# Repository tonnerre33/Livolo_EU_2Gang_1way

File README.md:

# Linovo_EU_2Gang_1way

## THIS NODE IS CURRENTLY IN DEVELOP
## YOU CAN SEE AND TEST THE DEV BRANCH AT YOUR OWN RISKS

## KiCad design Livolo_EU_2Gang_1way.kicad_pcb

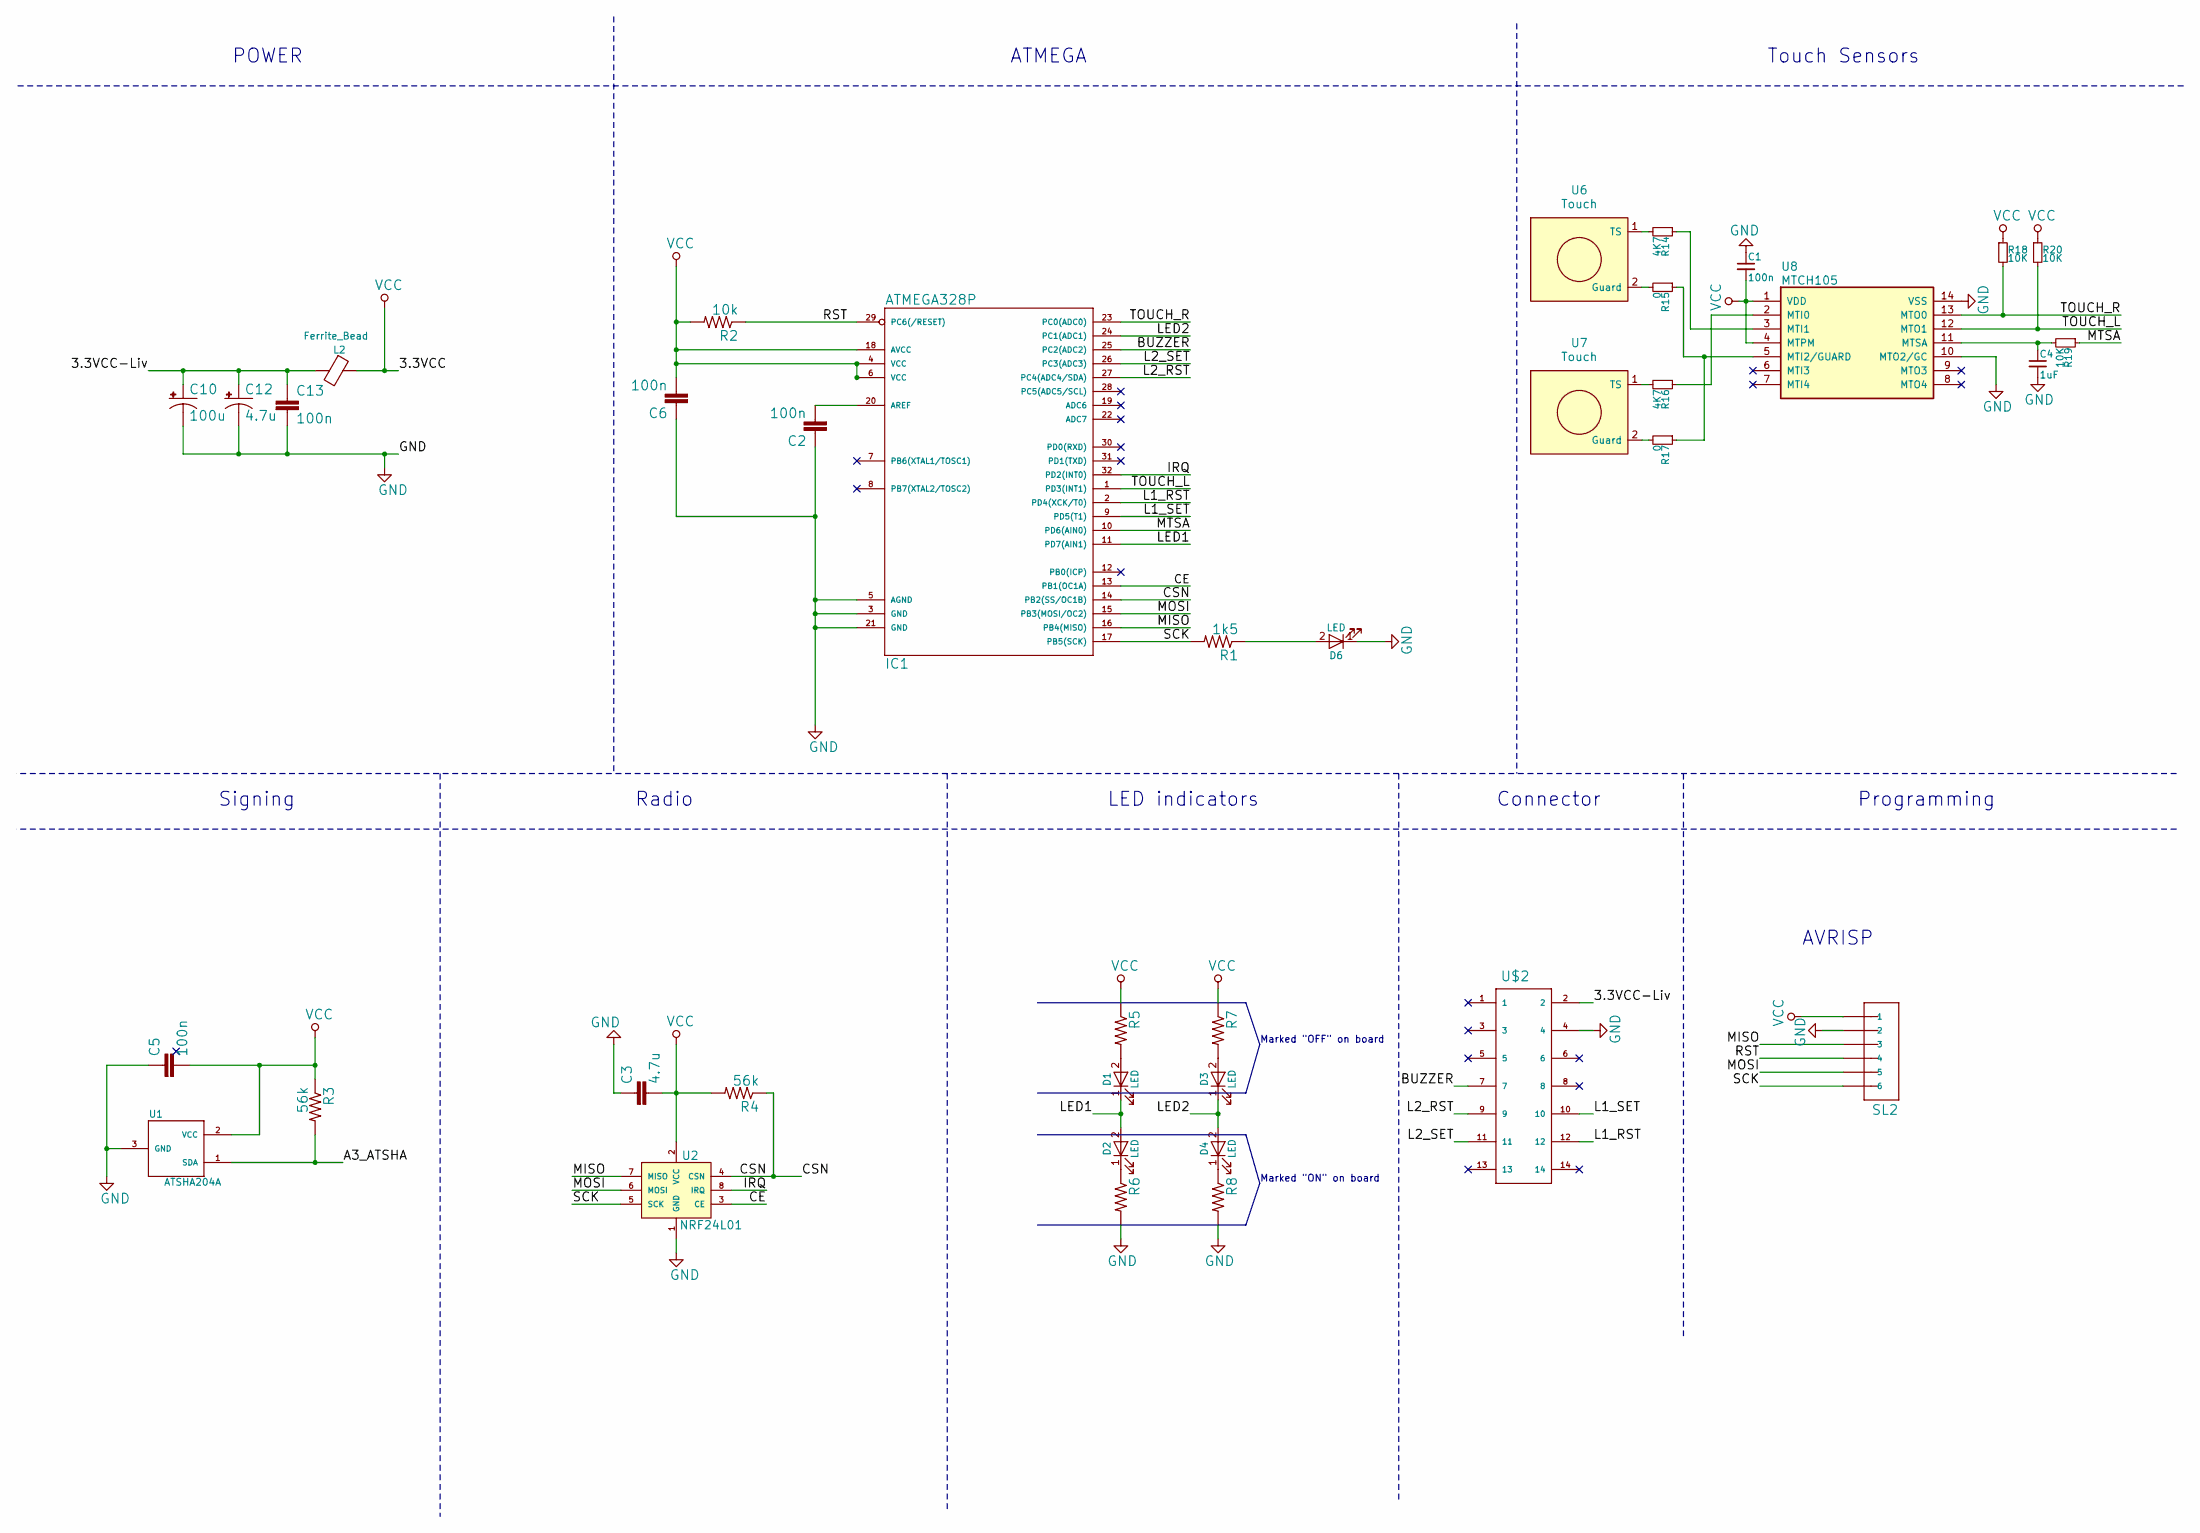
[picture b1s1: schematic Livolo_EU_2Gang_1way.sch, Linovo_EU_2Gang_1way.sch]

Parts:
C1, C5: 100n; C_0603_HandSoldering
C2, C6: 100n; C_0402
C3: 4.7u; C_0603_HandSoldering
C4: 1uF; C_0603_HandSoldering
C10: 100u; EIA3216; Rating X5R/10V
C12: 4.7u; EIA3216; Rating X5R/10V
C13: 100n; C_0603_HandSoldering; Rating X5R/10V
D1, D2, D3, D4, D6: LED; LED_0603
IC1: ATMEGA328P; TQFP32-08
L2: Ferrite_Bead; R_0603_HandSoldering
R1: 1k5; R_0603_HandSoldering
R2: 10k; R_0603_HandSoldering
R3, R4: 56k; R_0603_HandSoldering
R5, R6, R7, R8: R_0603_HandSoldering
R14, R16: 4K7; R_0603
R15, R17: 0; R_0603
R18, R19, R20: 10K; R_0603
SL2: 1X06-1MM
U1: ATSHA204A; SOT23-3
U2: NRF24L01; NRF24L01-SMD
U6, U7: Touch; livolo_ts_guard
U8: MTCH105; SSOP-14_5.3x6.2mm_Pitch0.65mm
U$2: CONNECTOR_02_X_072MM_SPACING; CONNECTOR_02_X_07_2MM

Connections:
/3.3VCC-Liv: C10.+, C12.+, C13.1, L2.2, U$2.2
/A3_ATSHA: R3.2, U1.1 (SDA)
/BUZZER: IC1.25 (PC2(ADC2)), U$2.7
/CE: IC1.13 (PB1(OC1A)), U2.3 (CE)
/CSN: IC1.14 (PB2(SS/OC1B)), R4.1, U2.4 (CSN)
/IRQ: IC1.32 (PD2(INT0)), U2.8 (IRQ)
/L1_RST: IC1.2 (PD4(XCK/T0)), U$2.12
/L1_SET: IC1.9 (PD5(T1)), U$2.10
/L2_RST: IC1.27 (PC4(ADC4/SDA)), U$2.9
/L2_SET: IC1.26 (PC3(ADC3)), U$2.11
/LED1: D1.1 (K), D2.2 (A), IC1.11 (PD7(AIN1))
/LED2: D3.1 (K), D4.2 (A), IC1.24 (PC1(ADC1))
/MISO: IC1.16 (PB4(MISO)), SL2.3, U2.7 (MISO)
/MOSI: IC1.15 (PB3(MOSI/OC2)), SL2.5, U2.6 (MOSI)
/MTSA: IC1.10 (PD6(AIN0)), R19.1
/RST: IC1.29 (PC6(/RESET)), R2.1, SL2.4
/SCK: IC1.17 (PB5(SCK)), R1.2, SL2.6, U2.5 (SCK)
/TOUCH_L: IC1.1 (PD3(INT1)), R20.2, U8.12 (MTO1)
/TOUCH_R: IC1.23 (PC0(ADC0)), R18.2, U8.13 (MTO0)
GND: C1.1, C2.1, C3.1, C4.2, C5.1, C6.1, C10.-, C12.-, C13.2, D6.1 (K), IC1.3 (GND), IC1.5 (AGND), IC1.21 (GND), R6.2, R8.2, SL2.2, U1.3 (GND), U2.1 (GND), U8.10 (MTO2/GC), U8.14 (VSS), U$2.4
unnamed: C2.2, IC1.20 (AREF)
unnamed: C4.1, R19.2, U8.11 (MTSA)
unnamed: D1.2 (A), R5.2
unnamed: D2.1 (K), R6.1
unnamed: D3.2 (A), R7.2
unnamed: D4.1 (K), R8.1
unnamed: D6.2 (A), R1.1
unnamed: R14.1, U8.3 (MTI1)
unnamed: R14.2, U6.1 (TS)
unnamed: R15.1, R17.1, U8.5 (MTI2/GUARD)
unnamed: R15.2, U6.2 (Guard)
unnamed: R16.1, U8.2 (MTI0)
unnamed: R16.2, U7.1 (TS)
unnamed: R17.2, U7.2 (Guard)
VCC: C1.2, C3.2, C5.2, C6.2, IC1.4 (VCC), IC1.6 (VCC), IC1.18 (AVCC), L2.1, R2.2, R3.1, R4.2, R5.1, R7.1, R18.1, R20.1, SL2.1, U1.2 (VCC), U2.2 (VCC), U8.1 (VDD), U8.4 (MTPM)

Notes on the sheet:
Programming
AVRISP
Touch Sensors
ATMEGA
POWER
Signing
Radio
LED indicators
Marked "OFF" on board
Marked "ON" on board
Connector

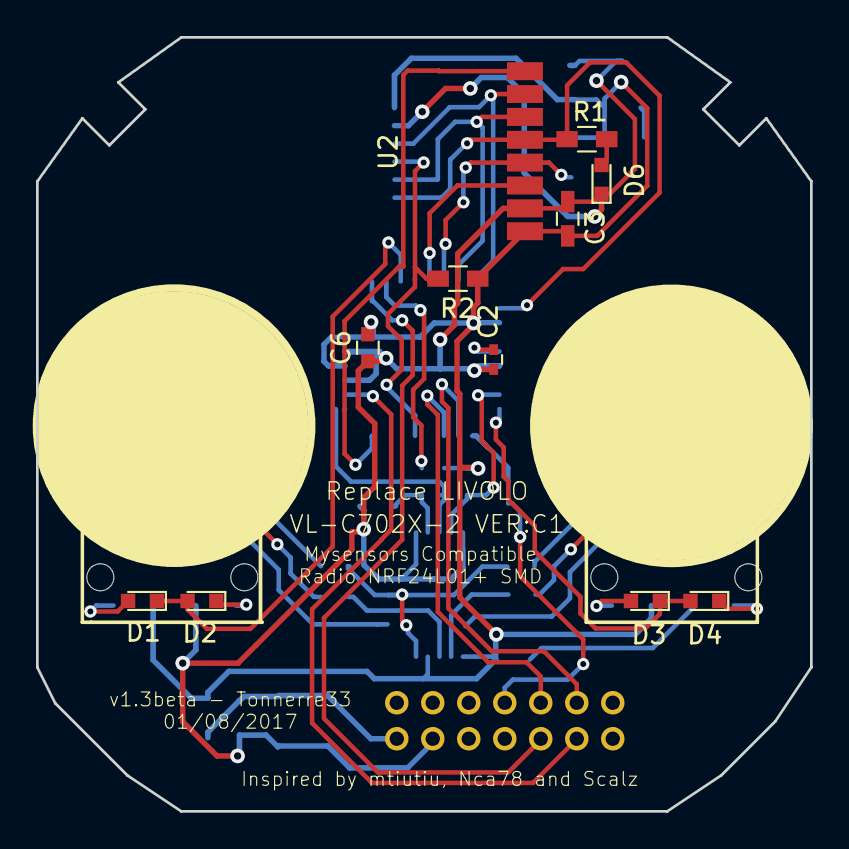
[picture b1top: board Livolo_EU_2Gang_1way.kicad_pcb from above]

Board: 2 copper layers, 43.0 x 43.0 mm, 38 parts (0 on the bottom side), 35 nets.

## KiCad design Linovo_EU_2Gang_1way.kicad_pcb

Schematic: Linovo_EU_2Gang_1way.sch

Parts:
C1, C2, C6: 100n; C_0402
C3: 10u; C_0603_HandSoldering
C4, C8: 0-50pF; C_0603_HandSoldering
C5, C7, C9: 100n; C_0603_HandSoldering
C10: 10u; EIA3216
C11: 100u; EIA3216
C12: 4.7u; EIA3216
D1, D2, D3, D4, D5, D6: LED0603; LED_0603
IC1: ATMEGA328P; TQFP32-08
R1, R9: 1k5; R_0603_HandSoldering
R2, R3: 10k; R_0603_HandSoldering
R4, R10: 56k; R_0603_HandSoldering
R5, R6, R7, R8: R_0603_HandSoldering
SL2, SL3: 1X06-1MM
U1: ATSHA204A; SOT23-3
U2: RFM69_MINIMAL; RFM69CW_MINIMAL
U$1, U$5: SENSOR_PAD_ROUND; SENSING_PAD_ROUND
U$2: CONNECTOR_02_X_072MM_SPACING; CONNECTOR_02_X_07_2MM
U$3: 8MHZ; RESONATOR-SMD
U$4, U$6: TTP223-BA6; SOT-23-6
U$7: RFM12B_ANTENNA; RFM12B-ANTENNA
U$8: AT25DF512C_MAHNT

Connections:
/A2: IC1.25 (PC2(ADC2)), U2.RESE
/A3_ATSHA: IC1.26 (PC3(ADC3)), R3.2, U1.1 (SDA)
/CSN: IC1.14 (PB2(SS/OC1B)), R4.1, U2.NSS
/D0_RX: IC1.30 (PD0(RXD)), SL3.4
/D1_TX: IC1.31 (PD1(TXD)), SL3.5
/DTR: C1.1, SL3.6
/FLASH_CS: IC1.12 (PB0(ICP)), R10.2, U$8.CS
/IRQ: IC1.32 (PD2(INT0)), U2.DIO0
/L1_RST: IC1.2 (PD4(XCK/T0)), U$2.12
/L1_SET: IC1.1 (PD3(INT1)), U$2.10
/L2_RST: IC1.9 (PD5(T1)), U$2.9
/L2_SET: IC1.10 (PD6(AIN0)), U$2.11
/LED1: D1.MINU, D3.PLUS, IC1.11 (PD7(AIN1))
/LED2: D2.MINU, D4.PLUS, IC1.13 (PB1(OC1A))
/MISO: IC1.16 (PB4(MISO)), SL2.3, U2.MISO, U$8.MISO
/MOSI: IC1.15 (PB3(MOSI/OC2)), SL2.5, U2.MOSI, U$8.MOSI
/N$1: D5.PLUS, R1.1
/N$2: IC1.7 (PB6(XTAL1/TOSC1)), U$3.1
/N$3: C4.2, U$1.SENS, U$4.3
/N$4: C2.2, IC1.20 (AREF)
/N$5: D1.PLUS, R5.2
/N$6: D3.MINU, R6.1
/N$7: D2.PLUS, R7.2
/N$8: IC1.8 (PB7(XTAL2/TOSC2)), U$3.3
/N$9: C8.2, U$5.SENS, U$6.3
/N$10: D4.MINU, R8.1
/N$11: D6.PLUS, R9.1
/N$12: IC1.27 (PC4(ADC4/SDA)), R9.2
/N$14: U2.ANT, U$7.P$1
/RST: C1.2, IC1.29 (PC6(/RESET)), R2.1, SL2.4
/SCK: IC1.17 (PB5(SCK)), R1.2, SL2.6, U2.SCK, U$8.SCK
/TOUCH_1: IC1.23 (PC0(ADC0)), U$4.1
/TOUCH_2: IC1.24 (PC1(ADC1)), U$6.1
GND: C2.1, C3.2, C4.1, C5.1, C6.1, C7.1, C8.1, C9.1, C10.-, C11.-, C12.-, D5.MINU, D6.MINU, IC1.3 (GND), IC1.5 (AGND), IC1.21 (GND), R6.2, R8.2, SL2.2, SL3.1, SL3.2, U1.3 (GND), U2.GND, U2.GND2, U$2.4, U$3.2, U$4.2, U$6.2, U$8.GND
VCC: C3.1, C5.2, C6.2, C7.2, C9.2, C10.+, C11.+, C12.+, IC1.4 (VCC), IC1.6 (VCC), IC1.18 (AVCC), R2.2, R3.1, R4.2, R5.1, R7.1, R10.1, SL2.1, SL3.3, U1.2 (VCC), U2.VDD, U$2.2, U$4.5, U$6.5, U$8.HOLD, U$8.VCC, U$8.WP

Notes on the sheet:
Programming
FTDI
AVRISP
Radio
ATMEGA
POWER
Signing
Touch Sensors
LED indicators
Marked "OFF" on board
Marked "ON" on board
OTA
Connector

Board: 2 copper layers, 45 parts (0 on the bottom side), 35 nets, no tracks yet.

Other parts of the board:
@HOLE0, @HOLE1, @HOLE2, @HOLE3: (no value)

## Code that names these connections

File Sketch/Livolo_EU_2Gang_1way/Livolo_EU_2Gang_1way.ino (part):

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int ledPins[] = {7,A1}; //{LED BP LEFT, LED BP RIGHT}
byte buttonPins[] = {3,A0}; //{BP LEFT, BP RIGHT}
const uint8_t RELAY_CH_PINS[][2] = {
    {5, 4}, // channel 1 relay control pins(bistable relay - 2 coils) {L1_SET, L1_RST}
    {A3, A4}  // channel 2 relay control pins(bistable relay - 2 coils) {L2_SET, L2_RST}
};
#define MTSA_PIN 6
#define BUZZER_PIN A2


const uint32_t RELAY_PULSE_DELAY_MS = 40; //Def 50
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    // initialize led, relays pins as outputs and buttons as inputs

    //SENSIBILITY
    pinMode(MTSA_PIN, OUTPUT);
    analogWrite(MTSA_PIN, 255 - settings.button_sensiblity * 255/100);
    //BUZZER
    pinMode(BUZZER_PIN, OUTPUT);
    digitalWrite(BUZZER_PIN, LOW);
    for (int i = 0; i < NUMBER_OF_BUTTONS; i++) {
        //LEDS
        pinMode(ledPins[i], OUTPUT);
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        if((millis() - lastMode) >= MODE_CLEANING_MS && MODE[i] == MODE_CLEANING) {
            MODE[0] = settings.mode_def[0];
            MODE[1] = settings.mode_def[1];
            blinkNumberOutput(1, BUZZER_PIN,100,100);
             for (int i = 0; i < NUMBER_OF_BUTTONS; i++) {
                digitalWrite(ledPins[i],  getChannelState(i));
             }
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                        switchLight(i+1, channelState[i]);
                        EndWaitFalseTrigger[i] = true;
                    } else {
                        blinkNumberOutput(1, BUZZER_PIN,100,100);
                    }
                }
            }
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                        MODE[i] = MODE_NORMAL;
                        channelState[i] = ON;
                        switchLight(i+1, channelState[i]); // No buzzer on the sleep power
                        blinkNumberOutput(2, BUZZER_PIN,100,100);
                    }
                    if(lastTouchTimestamp[i] >= LONG_TOUCH_DETECT_CLEANING_MS) {
                        MODE[0] = MODE_CLEANING;
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                        lastMode = millis();
                        channelState[i] = ON;
                        switchLight(i+1, channelState[i]); // No buzzer on the sleep power 
                        blinkNumberOutput(1, BUZZER_PIN,100,100);
                    }
                }
            }
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                if(millis() - lastTouchTimestamp[i] >= LONG_TOUCH_DETECT_THRESHOLD_MS && MODE[i] != MODE_NORMAL
                        && channelState[i] == ON) { // No buzzer on the sleep power
                    MODE[i] = MODE_NORMAL;
                    blinkNumberOutput(2, BUZZER_PIN,100,100);
                }
                if(millis() - lastTouchTimestamp[i] >= LONG_TOUCH_DETECT_CLEANING_MS && MODE[i] != MODE_CLEANING
                        && channelState[i] == ON) { // No buzzer on the sleep power
                    MODE[0] = MODE_CLEANING;
                    MODE[1] = MODE_CLEANING;
                    lastMode = millis();
                    blinkNumberOutput(1, BUZZER_PIN,100,100);
                }

            }
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
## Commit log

2017-03-26 First version of the PCB
2017-03-26 replace senspad & reroot
2017-03-26 Documentation Added
2017-03-26 Change value RFM69 capacitor
2017-04-01 Convert to Kicad
2017-04-01 Correct name project
2017-04-01 rootage
2017-04-01 Generate gerber files
2017-04-01 align sens pad
2017-04-01 update gerber
2017-04-01 move capacitor C11
2017-04-01 increase distance between pad and wire
2017-04-01 update gerber files
2017-04-01 saved schema but duno which modif
2017-04-02 move 14 pins connector
2017-04-02 cleanup schema
2017-04-02 Ceramic capacitor added in parrallel of Tantalum
2017-04-02 optimise position condensator senspad
2017-04-02 correct ERC errors
2017-04-02 optimise position C2
2017-04-02 capacitor added for OTA
2017-04-02 Text cleaning and Readme update
2017-04-02 Readme update
2017-04-08 power node by 12Vcc
2017-04-08 increase clearance netclass POWER from 8 to 10 mil
2017-04-08 cleaning
2017-04-08 replace bad footprint AT25DF512C
2017-04-08 Replace some capacitor 0402 -> 0603
2017-04-09 add documentation and BOM
2017-04-09 add ATMEGA328P doc
2017-04-09 update pdf schema
2017-04-15 Change FTDI wiring
2017-05-14 add doc
2017-06-12 Adding Sketch
2017-06-13 Change RFM69 by NRF24L01 cause crash
2017-06-13 Adding Symbols and footprint
2017-06-15 Sketch test
2017-06-16 version NRF24
2017-07-01 update sketch and adding TTP223 documentation
2017-07-29 change code
2017-07-29 replace TTP223 by MTCH105
2017-07-29 ajust silkscreen
2017-07-29 adding shunt for test with or without guard
2017-07-29 update version to v1.2 + pdf + gerber
2017-07-29 moving C6 for be closer of pin 4 and 5
2017-07-29 moving leds
2017-08-01 changes after mtiutiu advises! thx
2017-08-01 correct pin buzzer
2017-08-05 move sketch directory and correct radio text on pcb
2017-08-26 added instant mode
2017-08-26 move MTSA pin to a PWM pin of the ATMEGA
2017-08-26 remove resistor for guard
2017-10-04 optimize
2017-11-05 optimise code
2017-11-05 optimise code for settings by the air
